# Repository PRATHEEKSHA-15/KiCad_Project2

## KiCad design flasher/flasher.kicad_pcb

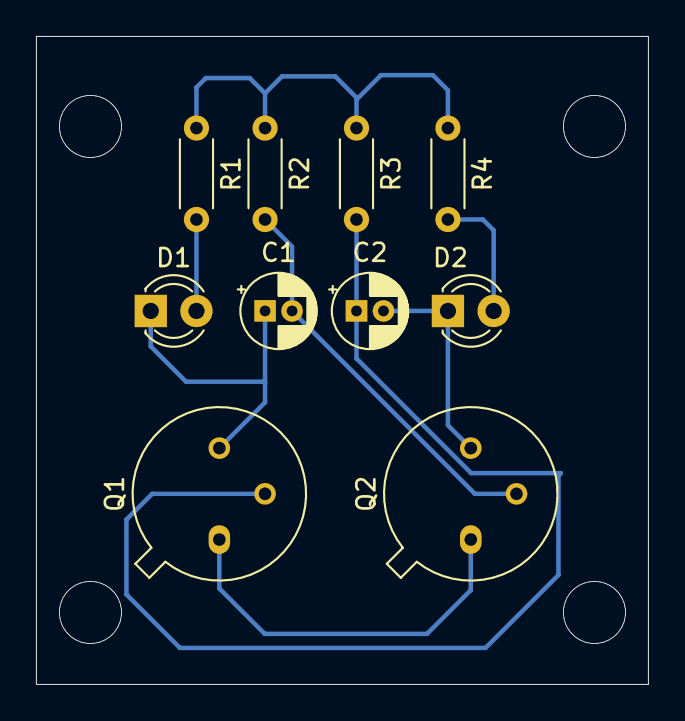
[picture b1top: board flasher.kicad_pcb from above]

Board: 2 copper layers, 34.0 x 36.0 mm, 10 parts (0 on the bottom side), 8 nets.

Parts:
C1, C2: C; CP_Radial_D4.0mm_P1.50mm
D1, D2: LED; LED_D3.0mm
Q1, Q2: 2N2219; TO-39-3
R1, R2, R3, R4: R_Small_US; R_Axial_DIN0204_L3.6mm_D1.6mm_P5.08mm_Horizontal

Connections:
Earth: Q1.1, Q2.1
unnamed: C1.1, D1.1, Q1.3
unnamed: C1.2, Q2.2, R2.2
unnamed: C2.1, Q1.2, R3.2
unnamed: C2.2, D2.1, Q2.3
unnamed: D1.2, R1.2
unnamed: D2.2, R4.2
VCC: R1.1, R2.1, R3.1, R4.1
